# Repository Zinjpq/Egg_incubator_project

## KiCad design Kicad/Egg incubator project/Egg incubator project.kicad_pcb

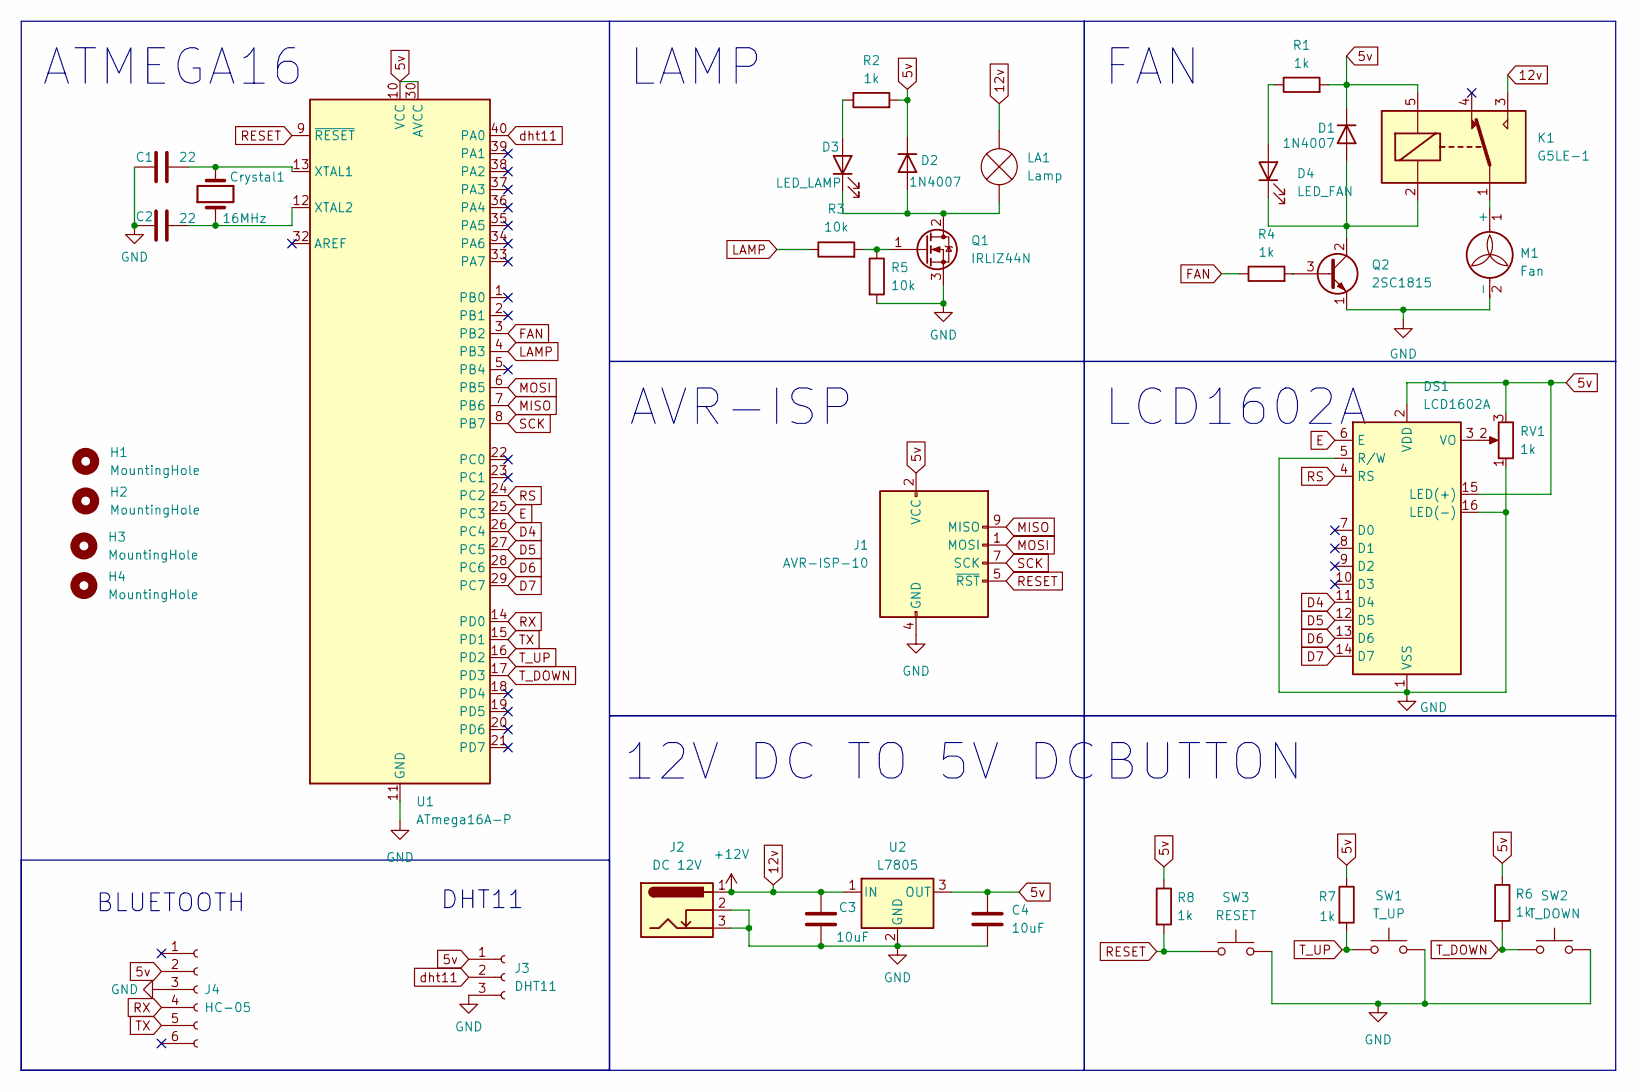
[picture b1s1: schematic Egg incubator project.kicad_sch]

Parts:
C1, C2: 22; C_Disc_D3.4mm_W2.1mm_P2.50mm
C3, C4: 10uF; CP_Radial_D5.0mm_P2.00mm
Crystal1: 16MHz; Crystal_HC49-4H_Vertical
D1, D2: 1N4007; D_DO-41_SOD81_P10.16mm_Horizontal
D3: LED_LAMP; LED_D3.0mm
D4: LED_FAN; LED_D3.0mm
DS1: LCD1602A; WC1602A
H1, H2, H3, H4: MountingHole; MountingHole_3mm
J1: AVR-ISP-10; IDC-Header_2x05_P2.54mm_Vertical
J2: DC 12V; BarrelJack_Horizontal
J3: DHT11; JST_PH_B3B-PH-K_1x03_P2.00mm_Vertical
J4: HC-05; PinSocket_1x06_P2.54mm_Vertical
K1: G5LE-1; Relay_SPDT_Omron-G5LE-1
LA1: Lamp; TE_440054-2_1x02_P2.00mm_Vertical
M1: Fan; TE_440054-2_1x02_P2.00mm_Vertical
Q1: IRLIZ44N; TO-220F-3_Horizontal_TabDown
Q2: 2SC1815; TO-92_Inline
R1, R2, R4, R6, R7, R8: 1k; R_Axial_DIN0204_L3.6mm_D1.6mm_P7.62mm_Horizontal
R3, R5: 10k; R_Axial_DIN0204_L3.6mm_D1.6mm_P7.62mm_Horizontal
RV1: 1k; Potentiometer_Bourns_3386F_Vertical
SW1: T_UP; SW_PUSH_6mm_H5mm
SW2: T_DOWN; SW_PUSH_6mm_H5mm
SW3: RESET; SW_PUSH_6mm_H5mm
U1: ATmega16A-P; DIP-40_W15.24mm
U2: L7805; TO-220-3_Horizontal_TabDown

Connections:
5v: C4.2, D1.1 (K), D2.1 (K), DS1.2 (VDD), DS1.15 (LED(+)), J1.2 (VCC), J3.1, J4.2, K1.5, R1.2, R2.2, R6.1, R7.1, R8.1, RV1.3, U1.10 (VCC), U1.30 (AVCC), U2.3 (OUT)
12v: C3.2, J2.1, K1.3, LA1.2 (+), U2.1 (IN)
D4: DS1.11 (D4), U1.26 (PC4)
D5: DS1.12 (D5), U1.27 (PC5)
D6: DS1.13 (D6), U1.28 (PC6)
D7: DS1.14 (D7), U1.29 (PC7)
E: DS1.6 (E), U1.25 (PC3)
FAN: R4.1, U1.3 (PB2)
GND: C1.1, C2.1, C3.1, C4.1, DS1.1 (VSS), DS1.5 (R/W), DS1.16 (LED(-)), J1.4 (GND), J1.6 (GND), J1.8 (GND), J1.10 (GND), J2.2, J2.3, J3.3, J4.3, M1.2 (-), Q1.3 (S), Q2.1 (E), R5.2, RV1.1, SW1.2, SW2.2, SW3.2, U1.11 (GND), U1.31 (GND), U2.2 (GND)
LAMP: R3.1, U1.4 (PB3)
MISO: J1.9 (MISO), U1.7 (PB6)
MOSI: J1.1 (MOSI), U1.6 (PB5)
unnamed: D1.2 (A), D4.1 (K), K1.2, Q2.2 (C)
unnamed: D2.2 (A), D3.1 (K), LA1.1 (-), Q1.2 (D)
unnamed: D3.2 (A), R2.1
unnamed: D4.2 (A), R1.1
unnamed: DS1.3 (VO), RV1.2
unnamed: K1.1, M1.1 (+)
unnamed: Q1.1 (G), R3.2, R5.1
unnamed: Q2.3 (B), R4.2
unnamed: C1.2, Crystal1.2, U1.13 (XTAL1)
unnamed: C2.2, Crystal1.1, U1.12 (XTAL2)
RESET: J1.5 (~RST), R8.2, SW3.1, U1.9 (~RESET)
RS: DS1.4 (RS), U1.24 (PC2)
RX: J4.4, U1.14 (PD0)
SCK: J1.7 (SCK), U1.8 (PB7)
TX: J4.5, U1.15 (PD1)
T_DOWN: R6.2, SW2.1, U1.17 (PD3)
T_UP: R7.2, SW1.1, U1.16 (PD2)
dht11: J3.2, U1.40 (PA0)

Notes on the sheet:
12V DC TO 5V DC
ATMEGA16
LAMP
LCD1602A
BUTTON
BLUETOOTH
DHT11
AVR-ISP
FAN

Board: 2 copper layers, 37 parts (0 on the bottom side), 30 nets, no tracks yet.

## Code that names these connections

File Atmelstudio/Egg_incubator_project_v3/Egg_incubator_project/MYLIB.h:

/*
 * mylib.h
 *
 * Created: 18/04/2024 10:46:47
 *  Author: Zinj
 */ 


#ifndef MYLIB_H_
#define MYLIB_H_

#include <stdint.h>
#include <avr/io.h>
#include <stdio.h>
#include <stdlib.h>
#include <util/delay.h>
#include <avr/interrupt.h> //Interrupt library

#define F_CPU 8000000UL

// LCD pin definition
#define LCD_RS		PC2
#define LCD_E		PC3
#define LCD_D4		PC4
#define LCD_D5		PC5
#define LCD_D6		PC6
#define LCD_D7		PC7
//fan and led
#define FAN			PB2
#define LAMP		PB3

int temp_set = 25; // Variable temp_set is used in ISR and bluetooth
int real_temp=0;

void lcd_command(uint8_t cmd) {
	PORTC = (cmd & 0xF0) | (1 << LCD_E);
	PORTC &= ~(1 << LCD_RS);
	_delay_ms(1);
	PORTC &= ~(1 << LCD_E);
	_delay_ms(1);

	PORTC = ((cmd & 0x0F) << 4) | (1 << LCD_E);
	PORTC &= ~(1 << LCD_RS);
	_delay_ms(1);
	PORTC &= ~(1 << LCD_E);
	_delay_ms(1);
}

void lcd_init(){
	_delay_ms(20);  /* LCD Power ON Initialization time >15ms */
	lcd_command (0x02); /* 4bit mode */
	lcd_command (0x28); /* Initialization of 16X2 LCD in 4bit mode */
	lcd_command (0x0C); /* Display ON Cursor OFF */
	lcd_command (0x06); /* Auto Increment cursor */
	lcd_command (0x01); /* Clear display */
	lcd_command (0x80); /* Cursor at home position */
}

void lcd_data(uint8_t data) {
	PORTC = (data & 0xF0) | (1 << LCD_E) | (1 << LCD_RS);
	_delay_ms(1);
	PORTC &= ~(1 << LCD_E);
	_delay_ms(1);

	PORTC = ((data & 0x0F) << 4) | (1 << LCD_E) | (1 << LCD_RS);
	_delay_ms(1);
	PORTC &= ~(1 << LCD_E);
	_delay_ms(1);
}

void lcd_string(const char* str) {
	int i = 0;
	while (str[i] != '\0') {
		lcd_data(str[i]);
		i++;
	}
}

void lcd_string_with_delay(const char* str ) {
	//clear screen
	lcd_command(0x01);
	int i = 0;
	while (str[i] != '\0') {
		if (i == 16) {
			lcd_command(0xC0);  // Move the cursor down to the second line
		}
		lcd_data(str[i]);
		i++;
		_delay_ms(30);
	}
}

void lcd_float(float number) {
	char str[10];
	char str_i[10];
	dtostrf(number, 2, 2, str_i);
	snprintf(str, sizeof(str), "%s", str_i);
	lcd_string(str);
}

void lcd_clear() {
	lcd_command(0x01);  // Clear LCD screen
}

void hello(){
	//Greeting
	lcd_string_with_delay("    Group 4     EMA3028 20 2024");
	_delay_ms(1000);
	lcd_string_with_delay(" The Incubator");
	_delay_ms(1000);
	lcd_command(0x01);  // Clear display
}

void updateDisplay(char* temp,char* humi, int temp_set) {
	//lcd_clear(); // Clear only if necessary
	lcd_command(0x80);
	lcd_string("T:");
	lcd_string (temp);
	lcd_string("*C");
	lcd_string(" H:");
	lcd_string (humi);
	lcd_string("%");
	lcd_command(0xC0); // Move cursor to second line

	lcd_string("set up: ");
	lcd_float(temp_set);
}

//dieu khien quat va den
void fan_control(float temp) {
	if (temp > temp_set) {
		PORTB |= (1 << FAN); // Turn fan on
		} else {
		PORTB &= ~(1 << FAN); // Turn fan off
	}
}

/*
// Micro controller sends start pulse/request /
void Request_dht11(){
	DDRA |= (1 << DHT11_PIN);
	PORTA &= ~(1 << DHT11_PIN); // set pin low 
	_delay_ms(20); // wait for 20ms 
	PORTA |= (1 << DHT11_PIN); // set pin high 
}

// Receive response from DHT11 
void Response_dht11(){
	DDRA &= ~(1 << DHT11_PIN);
	while (PINA & (1 << DHT11_PIN));
	while (!(PINA & (1 << DHT11_PIN)));
	while (PINA & (1 << DHT11_PIN));
}

// Receive data 
uint8_t Receive_data_dht11(){
	uint8_t c = 0;
	for (int q = 0; q < 8; q++) {
		while (!(PINA & (1 << DHT11_PIN))); // check received bit 0 or 1 
		_delay_us(30);
		if (PINA & (1 << DHT11_PIN)) // if high pulse is greater than 30ms 
		c = (c << 1) | (0x01); // then it's logic HIGH 
		else // otherwise it's logic LOW 
		c = (c << 1);
		while (PINA & (1 << DHT11_PIN));
	}
	return c;
}
*/

#endif /* MYLIB_H_ */

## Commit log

2024-08-10 First upload
2024-09-11 nothing
2024-09-15 chang image
2024-09-18 Test file kicad
2024-12-12 viết lại phần source code
2025-11-24 Update Linh kiện report spreadsheet
    Replaces the previous version of 'Linh kiện .xlsx' with an updated file. The specific changes within the spreadsheet are not detailed in this commit.
2026-02-04 big update, reconstruct folder
2026-02-04 update name
2026-02-04 create stm32 project and delete simulation proteus
